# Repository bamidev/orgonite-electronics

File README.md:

Orgonite Pyramid Firmware
=========================
This project consists of two pieces of firmware.
One for the LED-driving chip, and one for the Mobius coil driving chip.
Instructions on how to physically build the pyramid will be available soon.

The LED-driving firmware is build for the atmega328p chip.
The coil-driving firmware will be build for the attiny2313, and in the future possibly a smaller chip.

Requirements
------------
In order to build these firmwares, you need `avr-gcc`, `avrdude` and Python 3 installed.
Otherwise, `make` is obviously required.
Python is required because it generates some C code that defines the random field.

Building & Flashing
-------------------
To build the LED-driving chip's firmware, go into folder `led-driver`, and run `make`.
To flash the firmware on to the chip, the fuses need to be set once with `make setfuses`, and then the firmware can be flashed with `make flash`.
Both generally need administrator level access.
However, because everyone has a different programmer, you need to set the variable `PROGRAMMER_ID` in the makefile.
Also, if you programmer is not at `/dev/ttyUSB0`, you need to set `DEV_PATH` also.

An example of building and flashing the LED-driving chip with and stk500 programmer that is accessible on `/dev/ttyUSB1`:
```
make
sudo make setfuses PROGRAMMER_ID=stk500v2 DEV_PATH=/dev/ttyUSB1
sudo make flash PROGRAMMER_ID=stk500v2 DEV_PATH=/dev/ttyUSB1
```

Checking the random field
-------------------------
The LED driver make use of a (semi-)random field that got precompiled into the chip.
It uses this 'random field' to generate a semi-random map of colors that it will 'move over'.
That is how it decides the colors to use for the LED's at a particular time.

Running `make bitmap` in `led-driver`, will compile the C code with `gcc` into a binary that produces a bitmap file, and then runs it.
The bitmap will be placed in `led-driver/bin/random_field.bmp`.
The bitmap is smaller than the field that is actually used, because otherwise the resolution would be too big.

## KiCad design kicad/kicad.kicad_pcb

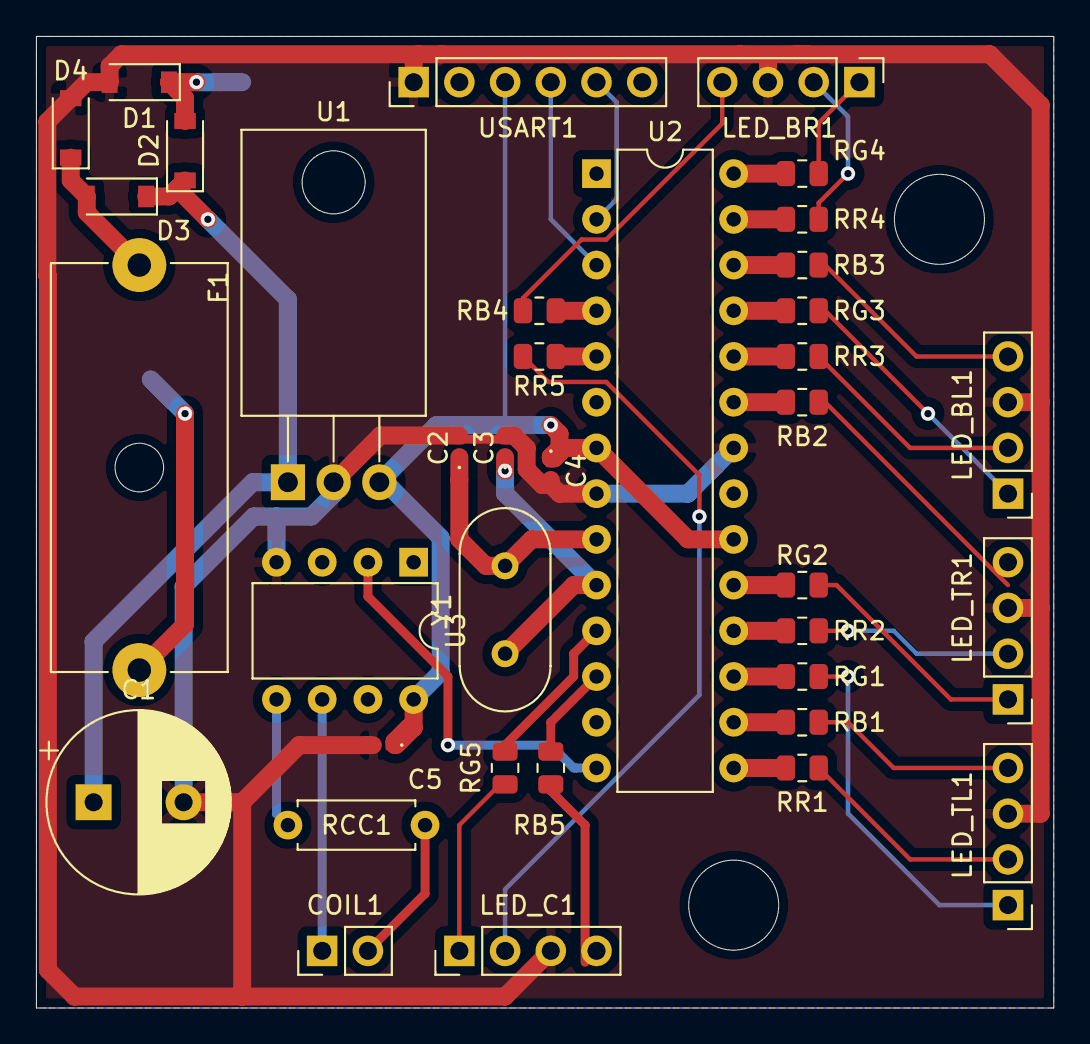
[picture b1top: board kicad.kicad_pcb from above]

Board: 2 copper layers, 56.5 x 54.0 mm, 37 parts (0 on the bottom side), 43 nets.

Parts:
C1: 1000uF; CP_Radial_D10.0mm_P5.00mm
C2, C3: 18pF; D_0402_1005Metric
C4, C5: 100nF; D_0402_1005Metric
COIL1: Conn_01x02_Male; PinHeader_1x02_P2.54mm_Vertical
D1: Schottky 1A; D_SOD-123
D2, D3, D4: D_Schottky; D_SOD-123
F1: Fuse; Fuseholder_Cylinder-5x20mm_Schurter_0031_8201_Horizontal_Op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
LED_BL1: Conn_01x04_Male; PinHeader_1x04_P2.54mm_Vertical
LED_BR1: Conn_01x04_Male; PinHeader_1x04_P2.54mm_Vertical
LED_C1: Conn_01x04_Male; PinHeader_1x04_P2.54mm_Vertical
LED_TL1: Conn_01x04_Male; PinHeader_1x04_P2.54mm_Vertical
LED_TR1: Conn_01x04_Male; PinHeader_1x04_P2.54mm_Vertical
RB1, RB2, RB3, RB4, RB5: 33Ω; R_0805_2012Metric
RCC1: 120Ω (4% or less); R_Axial_DIN0207_L6.3mm_D2.5mm_P7.62mm_Horizontal
RG1, RG2, RG3, RG4, RG5: 100Ω; R_0805_2012Metric
RR1, RR2, RR3, RR4, RR5: 150Ω; R_0805_2012Metric
U1: L7805; TO-220-3_Horizontal_TabDown
U2: ATmega328P-PU; DIP-28_W7.62mm
U3: ATtiny45-20PU; DIP-8_W7.62mm
USART1: Conn_01x06_Male; PinHeader_1x06_P2.54mm_Vertical
Y1: 16Mhz; Crystal_HC49-U_Vertical

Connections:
+1V5: C4.1, C5.1, U1.3, U2.7, U2.20, U3.8, USART1.3
GNDREF: C1.2, C2.2, C3.2, C4.2, C5.2, D1.2, D4.2, LED_BL1.3, LED_BR1.3, LED_C1.3, LED_TL1.3, LED_TR1.3, U1.2, U2.8, U2.22, U3.4, USART1.1
unnamed: C1.1, D2.1, D3.1, U1.1
unnamed: C2.1, U2.9, Y1.2
unnamed: C3.1, U2.10, Y1.1
unnamed: COIL1.1, U3.6
unnamed: COIL1.2, RCC1.2
unnamed: D1.1, D2.2
unnamed: D3.2, D4.1, F1.1
unnamed: LED_BL1.1, RG3.2
unnamed: LED_BL1.2, RR3.2
unnamed: LED_BL1.4, RB3.2
unnamed: LED_BR1.1, RG4.2
unnamed: LED_BR1.2, RR4.2
unnamed: LED_BR1.4, RB4.2
unnamed: LED_C1.1, RG5.2
unnamed: LED_C1.2, RR5.2
unnamed: LED_C1.4, RB5.2
unnamed: LED_TL1.1, RG1.2
unnamed: LED_TL1.2, RR1.2
unnamed: LED_TL1.4, RB1.2
unnamed: LED_TR1.1, RG2.2
unnamed: LED_TR1.2, RR2.2
unnamed: LED_TR1.4, RB2.2
unnamed: RB1.1, U2.16
unnamed: RB2.1, U2.23
unnamed: RB3.1, U2.26
unnamed: RB4.1, U2.4
unnamed: RB5.1, U2.12
unnamed: RCC1.1, U3.5
unnamed: RG1.1, U2.17
unnamed: RG2.1, U2.19
unnamed: RG3.1, U2.25
unnamed: RG4.1, U2.28
unnamed: RG5.1, U2.11
unnamed: RR1.1, U2.15
unnamed: RR2.1, U2.18
unnamed: RR3.1, U2.24
unnamed: RR4.1, U2.27
unnamed: RR5.1, U2.5
unnamed: U2.2, USART1.5
unnamed: U2.3, USART1.4
unnamed: U2.14, U3.2

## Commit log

2021-09-06 Second commit. This is the code that is now actually used on the LED-driver chip.
2021-09-06 Fixed README code indentation.
2021-09-06 Fixed README file extension
2021-09-06 Updated the fuse bits to use longer startup time and clock output pin and brown out detection.
2021-09-06 Fixed the timer num. of cycles for the 1s interval. What 1 cycle too much.
2021-09-06 Added the coil-driving firmware.
2021-09-11 Changed pin functions and fixed issue with corner_tl led that went too slow.
2021-09-19 Changed the target chip for the coil driver to an attiny45 instead of the attiny2313. This is pretty much the smaller through-hole avr chip available capable of 16Mhz. By doing so, I also had to chan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
2021-09-19 Redo of the simulated PWM code, to prevent flashes of the non-true-pwm leds.
2021-09-19 Fixed an issue where the colors would not join together at the boundaries.
2021-09-25 Added kicad project. Complete with circuit diagram, PCB layout and JLCPCB component tags.
2021-09-25 Added untested code to implement a function generator that is accurate enough to generate any function at least for 7.83 as a frequency..
2021-09-26 Added the code for square wave generation to the coil driver.
2021-10-02 Fixed frequency of coil driver.
